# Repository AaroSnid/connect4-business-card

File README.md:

# Connect 4 Business Card

This business card doubles as a portable, handheld gaming device that allows a user to play game of Connect 4 against an onboard AI bot. Built on the STM32 platform, it features a custom 7x6 bicolor LED grid and a low-leakage power system designed for maximizing battery life.

> **Status:** Hardware V1.0 Release 
> **Hardware Version:** V1.0

---

## Features

- **Strategic Gameplay**
  - Play against a programmed AI bot on a microcontroller. You can select the difficulty and starting player through startup configurations.
  - 7x6 bicolor LED grid representing the game board. Player pieces are shown in Red / Orange

- **Dual Power Options**
  - **Battery Mode:** Optimized for a CR2032 coin cell for maximum portability.
  - **High-Performance Mode:** USB-C power input automatically boosts clock frequency for faster AI move processing. (Upcoming)

- **Power Management**
  - Physical slide switch for hard battery disconnection to prevent leakage current.
  - Integrated under-voltage and brown-out protection (BOR/POR/PDR).

- **Advanced Display Control**
  - 42 bicolor LEDs (84 total elements) routed antiparallel for layout efficiency.
  - Hardware-accelerated screen refreshing using timer triggered DMA writes to minimize CPU overhead.

- **Optimized Inputs**
  - 7 dedicated column buttons for move selection.
  - Software debouncing by limiting input registration windows.

---

## Bill of Materials (Summary)

| Item             | Part Number           | Qty | Notes                          |
|------------------|-----------------------|-----|--------------------------------|
| MCU              | STM32U073CCU6         | 1   | Ultra-low-power ARM Cortex-M0+ |
| Bicolor LEDs     | P4-1615ROTCA1-0.6T    | 42  | Red/Orange SMD LEDs            |
| Battery Holder   | Keystone 3002         | 1   | For CR2032 Coin Cell           |
| USB-C Connector  | SHOU HAN C2765186     | 1   | 16-pin Power/Data Delivery     |
| LDO Regulator    | MCP1700T-3002E/TT     | 1   | Low Quiescent Current 3.0V     |
| Input Buttons    | TSB008A2518A          | 7   | Ultra-thin NO buttons          |
| Power Switch     | MSK12C02-HB           | 1   | Battery/USB-C Selection        |

---

## Hardware Subsystems

### Power Supply

- **Primary:** CR2032 Coin Cell.
- **Secondary:** USB-C (5V) regulated through an MCP1700 LDO.
- **Switching:** A physical SPDT switch toggles between sources. The "ON" position selects the battery, while "OFF" selects USB-C, ensuring the battery is physically disconnected when using external power.
- **Monitoring:** The STM32 utilizes its internal POR/PDR/BOR peripherals to monitor voltage levels and provide under-voltage protection.

---

### Microcontroller (STM32U073CCU6)

- **Architecture:** Ultra-low-power high-performance MCU.
- **Clock Management:** (Upcoming)
  - **Battery Mode:** Lower frequency to conserve energy.
  - **USB Mode:** Increased clock frequency for "intense" AI computation.

**Key Peripherals**

| Function         | Peripheral      | Notes                                  |
|------------------|-----------------|----------------------------------------|
| LED Matrix       | GPIO Port B     | Direct register writes for speed       |
| Refresh Timing   | Hardware Timer  | Triggers DMA transfers                 |
| Data Transfer    | DMA             | Automated GPIO updates                 |
| User Inputs      | EXTI (1-7)      | Pull-down resistors on Port A          |
| Firmware Update  | USB-C (DFU)     | Native USB 2.0 bootloader support      |
| Debug            | SWD             | Standard programming interface         |

---

### Display Implementation

The display consists of 42 bicolor LEDs wired in an antiparallel configuration.
- **Efficiency:** LEDs share pins to reduce the required GPIO count.
- **Refresh Logic:** A hardware timer triggers a DMA stream that performs direct register writes to GPIO Port B. This ensures a flicker-free display without taxing the main CPU core.

---

### Inputs & UI

- **Buttons:** 7 tactile switches corresponding to the 7 columns of the Connect 4 board.
- **Debouncing:** Handled via software flags within an Interrupt Service Routine (ISR). The system clears the flag just before the player turn for software input debouncing.

---

## Firmware Architecture

### Overview

The firmware is designed for efficiency and responsiveness. 
On startup, the MCU reads the buttons to get startup config values. The rightmost button will select the AI going first, and the others select the difficulty from 1-6 (default 5)
The main game loop handles the Connect-4 logic, while the display refresh is handled entirely in the background via timer triggered DMA.

### Programming

- **Debug:** A standard SWD header is provided for real-time debugging and initial flashing.

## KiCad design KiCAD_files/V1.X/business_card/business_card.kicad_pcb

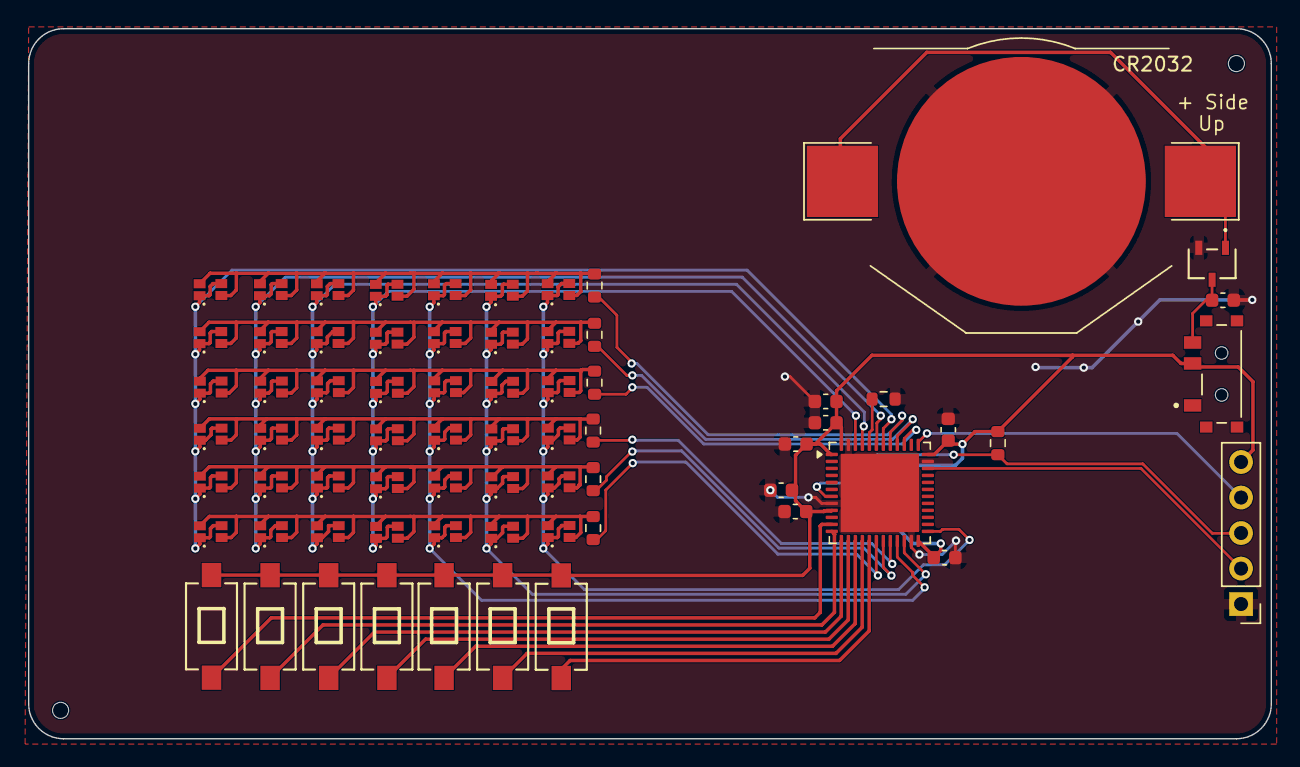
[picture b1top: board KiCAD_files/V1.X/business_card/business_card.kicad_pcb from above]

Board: 2 copper layers, 88.9 x 50.8 mm, 72 parts (0 on the bottom side), 35 nets.

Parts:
BT1: CR2032; BatteryHolder_Keystone_3002_1x2032
C1: 47uF; C_0603_1608Metric
C5, C10: 4.7uF; C_0603_1608Metric
C6, C7, C11: 100nF; C_0603_1608Metric
C8: 10nF; C_0603_1608Metric
C9: 1uF; C_0603_1608Metric
D1, D2, D3, D4, D5, D6, D7, D8, D9, D10, D11, D12, D13, D14, D15, D16, D17, D18, D19, D20, D21, D22, D23, D24, D25, D26, D27, D28, D29, D30, D31, D32, D33, D34, D35, D36, D37, D38, D39, D40, D41, D42: LED_CHIP
H1, H1#2: MountingHole; ToolingHole_1.152mm
J2: Conn_01x05_Pin; PinHeader_1x05_P2.54mm_Vertical
Q1: AO3401A; SOT-23-3L_AOS-L
R3, R4, R5, R6, R7, R8: 250; R_0603_1608Metric
R9, R10: 10K; R_0603_1608Metric
S1: MSK12C02; SW_MSK12C02
SW1, SW2, SW3, SW4, SW5, SW6, SW7: SW_Push; TSB008A2526A
U1: STM32U073CCUx; QFN-48-1EP_7x7mm_P0.5mm_EP5.6x5.6mm

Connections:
/COL1: D1.1, D1.3, D8.1, D8.3, D15.1, D15.3, D22.1, D22.3, D29.1, D29.3, D36.1, D36.3, U1.42 (PB6)
/COL2: D2.1, D2.3, D9.1, D9.3, D16.1, D16.3, D23.1, D23.3, D30.1, D30.3, D37.1, D37.3, U1.43 (PB7)
/COL3: D3.1, D3.3, D10.1, D10.3, D17.1, D17.3, D24.1, D24.3, D31.1, D31.3, D38.1, D38.3, U1.45 (PB8)
/COL4: D4.1, D4.3, D11.1, D11.3, D18.1, D18.3, D25.1, D25.3, D32.1, D32.3, D39.1, D39.3, U1.46 (PB9)
/COL5: D5.1, D5.3, D12.1, D12.3, D19.1, D19.3, D26.1, D26.3, D33.1, D33.3, D40.1, D40.3, U1.21 (PB10)
/COL6: D6.1, D6.3, D13.1, D13.3, D20.1, D20.3, D27.1, D27.3, D34.1, D34.3, D41.1, D41.3, U1.22 (PB11)
/COL7: D7.1, D7.3, D14.1, D14.3, D21.1, D21.3, D28.1, D28.3, D35.1, D35.3, D42.1, D42.3, U1.25 (PB12)
/INPUT_1: SW1.1, U1.11 (PA1)
/INPUT_2: SW2.1, U1.12 (PA2)
/INPUT_3: SW3.1, U1.13 (PA3)
/INPUT_4: SW4.1, U1.14 (PA4)
/INPUT_5: SW5.1, U1.15 (PA5)
/INPUT_6: SW6.1, U1.16 (PA6)
/INPUT_7: SW7.1, U1.17 (PA7)
/NRST: J2.3, R10.2, U1.7 (PF2)
/ROW1: R3.2, U1.41 (PB5)
/ROW2: R4.2, U1.40 (PB4)
/ROW3: R5.2, U1.39 (PB3)
/ROW4: R6.2, U1.20 (PB2)
/ROW5: R7.2, U1.19 (PB1)
/ROW6: R8.2, U1.18 (PB0)
/SWCLK: J2.4, U1.37 (PA14)
/SWDIO: J2.2, U1.34 (PA13)
GND: BT1.2 (-), C1.2, C5.2, C6.2, C7.2, C8.2, C9.2, C10.2, C11.2, J2.1, Q1.2 (G), R9.2, U1.8 (VSSA), U1.23 (VSS), U1.35 (VSS), U1.47 (VSS), U1.49 (VSS)
unnamed: BT1.1 (+), Q1.1 (D)
unnamed: D1.2, D1.4, D2.2, D2.4, D3.2, D3.4, D4.2, D4.4, D5.2, D5.4, D6.2, D6.4, D7.2, D7.4, R3.1
unnamed: D8.2, D8.4, D9.2, D9.4, D10.2, D10.4, D11.2, D11.4, D12.2, D12.4, D13.2, D13.4, D14.2, D14.4, R4.1
unnamed: D15.2, D15.4, D16.2, D16.4, D17.2, D17.4, D18.2, D18.4, D19.2, D19.4, D20.2, D20.4, D21.2, D21.4, R5.1
unnamed: D22.2, D22.4, D23.2, D23.4, D24.2, D24.4, D25.2, D25.4, D26.2, D26.4, D27.2, D27.4, D28.2, D28.4, R6.1
unnamed: D29.2, D29.4, D30.2, D30.4, D31.2, D31.4, D32.2, D32.4, D33.2, D33.4, D34.2, D34.4, D35.2, D35.4, R7.1
unnamed: D36.2, D36.4, D37.2, D37.4, D38.2, D38.4, D39.2, D39.4, D40.2, D40.4, D41.2, D41.4, D42.2, D42.4, R8.1
unnamed: C1.1, Q1.3 (S), S1.3
unnamed: S1.4_1 (GND), S1.4_2 (GND), S1.4_3 (GND), S1.4_4 (GND)
unnamed: R9.1, U1.44 (PF3)
VDD: C5.1, C6.1, C7.1, C8.1, C9.1, C10.1, C11.1, J2.5, R10.1, S1.2, SW1.2, SW2.2, SW3.2, SW4.2, SW5.2, SW6.2, SW7.2, U1.1 (VBAT), U1.9 (VDDA), U1.24 (VDD), U1.36 (VDDUSB), U1.48 (VDD)

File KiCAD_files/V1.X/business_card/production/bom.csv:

Designator,Footprint,Quantity,Value,LCSC Part #
BT1,BatteryHolder_Keystone_3002_1x2032,1,CR2032,
"C1, C10, C5",0603,3,4.7uF,
"C11, C6, C7",0603,3,100nF,
"C2, C3, C4, C9",0603,4,1uF,
C8,0603,1,10nF,
"D1, D10, D11, D12, D13, D14, D15, D16, D17, D18, D19, D2, D20, D21, D22, D23, D24, D25, D26, D27, D28, D29, D3, D30, D31, D32, D33, D34, D35, D36, D37, D38, D39, D4, D40, D41, D42, D5, D6, D7, D8, D9",LED_CHIP,42,~,
J1,USB-C-SMD_TYPE-C-6PIN-2MD-073,1,USB_C_Receptacle_USB2.0_14P,
J2,PinHeader_1x05_P1.00mm_Vertical,1,Conn_01x05_Pin,
"R1, R2",0603,2,5.1K,
"R10, R9",0603,2,10K,
"R3, R4, R5, R6, R7, R8",0603,6,250,
S1,SW_MSK12C02,1,MSK12C02,
"SW1, SW2, SW3, SW4, SW5, SW6, SW7",TSB008A2526A,7,SW_Push,
SW8,SW-SMD_4P-L2.6-W1.6-P0.75-LS3.0,1,SW_MEC_5E,
TP1,TestPoint_THTPad_D1.0mm_Drill0.5mm,1,VDDUSB,
TP2,TestPoint_THTPad_D1.0mm_Drill0.5mm,1,GND,
TP3,TestPoint_THTPad_D1.0mm_Drill0.5mm,1,VDD,
U1,QFN-48-1EP_7x7mm_P0.5mm_EP5.6x5.6mm,1,STM32U073CCUx,
U2,SOT-23,1,MCP1700x-300xxTT,

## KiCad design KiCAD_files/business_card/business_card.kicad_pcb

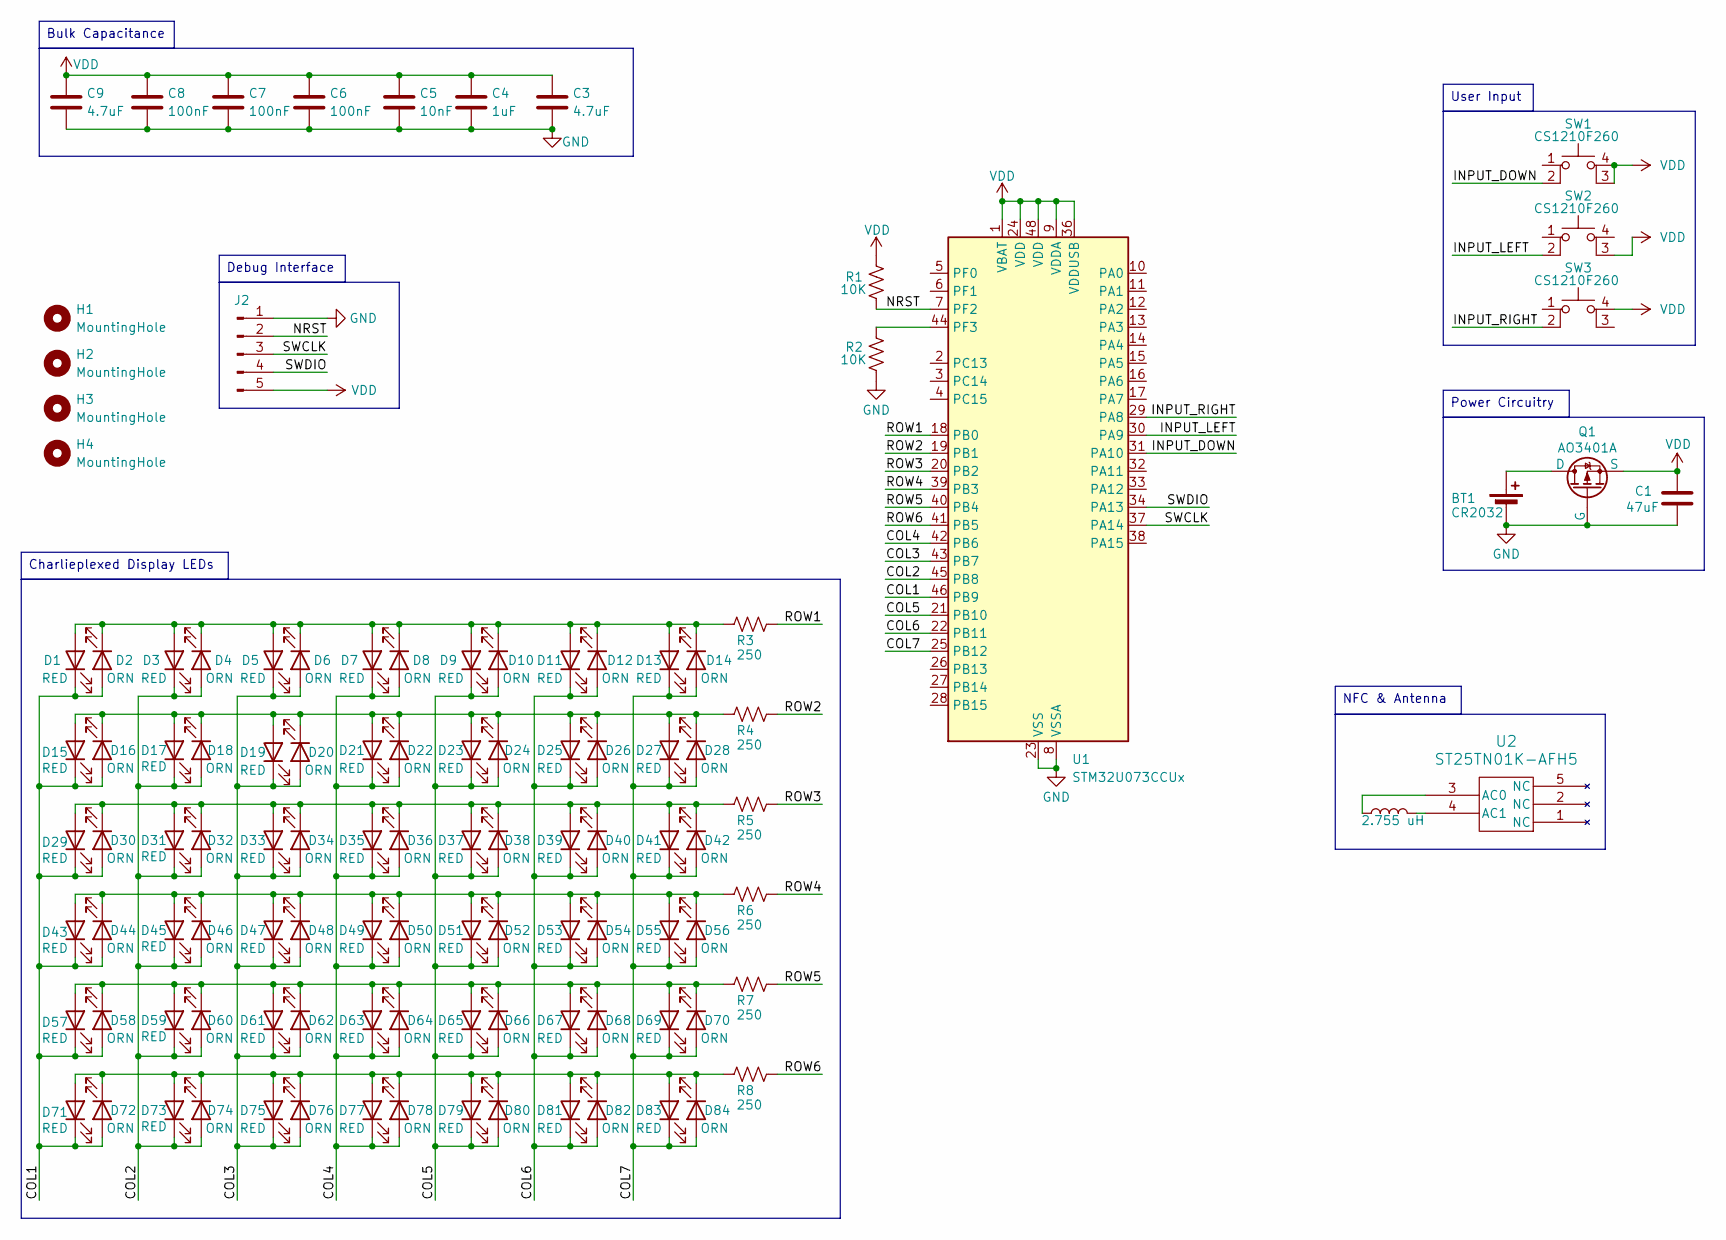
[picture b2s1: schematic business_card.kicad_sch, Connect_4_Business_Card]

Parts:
BT1: CR2032; BAT_BAT-HLD-005-THM
C1: 47uF; C_0603_1608Metric
C3, C9: 4.7uF; C_0603_1608Metric
C4: 1uF; C_0603_1608Metric
C5: 10nF; C_0603_1608Metric
C6, C7, C8: 100nF; C_0603_1608Metric
D1, D3, D5, D7, D9, D11, D13, D15, D17, D19, D21, D23, D25, D27, D29, D31, D33, D35, D37, D39, D41, D43, D45, D47, D49, D51, D53, D55, D57, D59, D61, D63, D65, D67, D69, D71, D73, D75, D77, D79, D81, D83: RED; LED_0603_1608Metric
D2, D4, D6, D8, D10, D12, D14, D16, D18, D20, D22, D24, D26, D28, D30, D32, D34, D36, D38, D40, D42, D44, D46, D48, D50, D52, D54, D56, D58, D60, D62, D64, D66, D68, D70, D72, D74, D76, D78, D80, D82, D84: ORN; LED_0603_1608Metric
H1, H2, H3, H4: MountingHole; ToolingHole_1.152mm
J2: Conn_01x05_Pin; PinHeader_1x05_P2.54mm_Vertical
L1: 2.755 uH; 25X48MM_NFC
Q1: AO3401A; SOT-23-3L_AOS-L
R1, R2: 10K; R_0603_1608Metric
R3, R4, R5, R6, R7, R8: 250; R_0603_1608Metric
SW1, SW2, SW3: CS1210F260; SW4_CS1210F260_CRS
U1: STM32U073CCUx; QFN-48-1EP_7x7mm_P0.5mm_EP5.6x5.6mm
U2: ST25TN01K-AFH5; UFDFPN-5_1P8X1P5_STM

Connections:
/COL1: D1.1 (K), D2.2 (A), D15.1 (K), D16.2 (A), D29.1 (K), D30.2 (A), D43.1 (K), D44.2 (A), D57.1 (K), D58.2 (A), D71.1 (K), D72.2 (A), U1.46 (PB9)
/COL2: D3.1 (K), D4.2 (A), D17.1 (K), D18.2 (A), D31.1 (K), D32.2 (A), D45.1 (K), D46.2 (A), D59.1 (K), D60.2 (A), D73.1 (K), D74.2 (A), U1.45 (PB8)
/COL3: D5.1 (K), D6.2 (A), D19.1 (K), D20.2 (A), D33.1 (K), D34.2 (A), D47.1 (K), D48.2 (A), D61.1 (K), D62.2 (A), D75.1 (K), D76.2 (A), U1.43 (PB7)
/COL4: D7.1 (K), D8.2 (A), D21.1 (K), D22.2 (A), D35.1 (K), D36.2 (A), D49.1 (K), D50.2 (A), D63.1 (K), D64.2 (A), D77.1 (K), D78.2 (A), U1.42 (PB6)
/COL5: D9.1 (K), D10.2 (A), D23.1 (K), D24.2 (A), D37.1 (K), D38.2 (A), D51.1 (K), D52.2 (A), D65.1 (K), D66.2 (A), D79.1 (K), D80.2 (A), U1.21 (PB10)
/COL6: D11.1 (K), D12.2 (A), D25.1 (K), D26.2 (A), D39.1 (K), D40.2 (A), D53.1 (K), D54.2 (A), D67.1 (K), D68.2 (A), D81.1 (K), D82.2 (A), U1.22 (PB11)
/COL7: D13.1 (K), D14.2 (A), D27.1 (K), D28.2 (A), D41.1 (K), D42.2 (A), D55.1 (K), D56.2 (A), D69.1 (K), D70.2 (A), D83.1 (K), D84.2 (A), U1.25 (PB12)
/INPUT_DOWN: SW1.2, U1.31 (PA10)
/INPUT_LEFT: SW2.2, U1.30 (PA9)
/INPUT_RIGHT: SW3.2, U1.29 (PA8)
/NRST: J2.2, R1.2, U1.7 (PF2)
/ROW1: R3.2, U1.18 (PB0)
/ROW2: R4.2, U1.19 (PB1)
/ROW3: R5.2, U1.20 (PB2)
/ROW4: R6.2, U1.39 (PB3)
/ROW5: R7.2, U1.40 (PB4)
/ROW6: R8.2, U1.41 (PB5)
/SWCLK: J2.3, U1.37 (PA14)
/SWDIO: J2.4, U1.34 (PA13)
GND: BT1.2 (-), C1.2, C3.2, C4.2, C5.2, C6.2, C7.2, C8.2, C9.2, J2.1, Q1.2 (G), R2.2, U1.8 (VSSA), U1.23 (VSS), U1.35 (VSS), U1.47 (VSS), U1.49 (VSS)
unnamed: BT1.1 (+), Q1.1 (D)
unnamed: D1.2 (A), D2.1 (K), D3.2 (A), D4.1 (K), D5.2 (A), D6.1 (K), D7.2 (A), D8.1 (K), D9.2 (A), D10.1 (K), D11.2 (A), D12.1 (K), D13.2 (A), D14.1 (K), R3.1
unnamed: D15.2 (A), D16.1 (K), D17.2 (A), D18.1 (K), D19.2 (A), D20.1 (K), D21.2 (A), D22.1 (K), D23.2 (A), D24.1 (K), D25.2 (A), D26.1 (K), D27.2 (A), D28.1 (K), R4.1
unnamed: D29.2 (A), D30.1 (K), D31.2 (A), D32.1 (K), D33.2 (A), D34.1 (K), D35.2 (A), D36.1 (K), D37.2 (A), D38.1 (K), D39.2 (A), D40.1 (K), D41.2 (A), D42.1 (K), R5.1
unnamed: D43.2 (A), D44.1 (K), D45.2 (A), D46.1 (K), D47.2 (A), D48.1 (K), D49.2 (A), D50.1 (K), D51.2 (A), D52.1 (K), D53.2 (A), D54.1 (K), D55.2 (A), D56.1 (K), R6.1
unnamed: D57.2 (A), D58.1 (K), D59.2 (A), D60.1 (K), D61.2 (A), D62.1 (K), D63.2 (A), D64.1 (K), D65.2 (A), D66.1 (K), D67.2 (A), D68.1 (K), D69.2 (A), D70.1 (K), R7.1
unnamed: D71.2 (A), D72.1 (K), D73.2 (A), D74.1 (K), D75.2 (A), D76.1 (K), D77.2 (A), D78.1 (K), D79.2 (A), D80.1 (K), D81.2 (A), D82.1 (K), D83.2 (A), D84.1 (K), R8.1
unnamed: R2.1, U1.44 (PF3)
unnamed: L1.1, U2.3 (AC0)
unnamed: L1.2, U2.4 (AC1)
VDD: C1.1, C3.1, C4.1, C5.1, C6.1, C7.1, C8.1, C9.1, J2.5, Q1.3 (S), R1.1, SW1.3 (K), SW1.4 (A), SW2.3 (K), SW3.4 (A), U1.1 (VBAT), U1.9 (VDDA), U1.24 (VDD), U1.36 (VDDUSB), U1.48 (VDD)

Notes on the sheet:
Bulk Capacitance
Charlieplexed Display LEDs
Power Circuitry
User Input
NFC & Antenna
Debug Interface

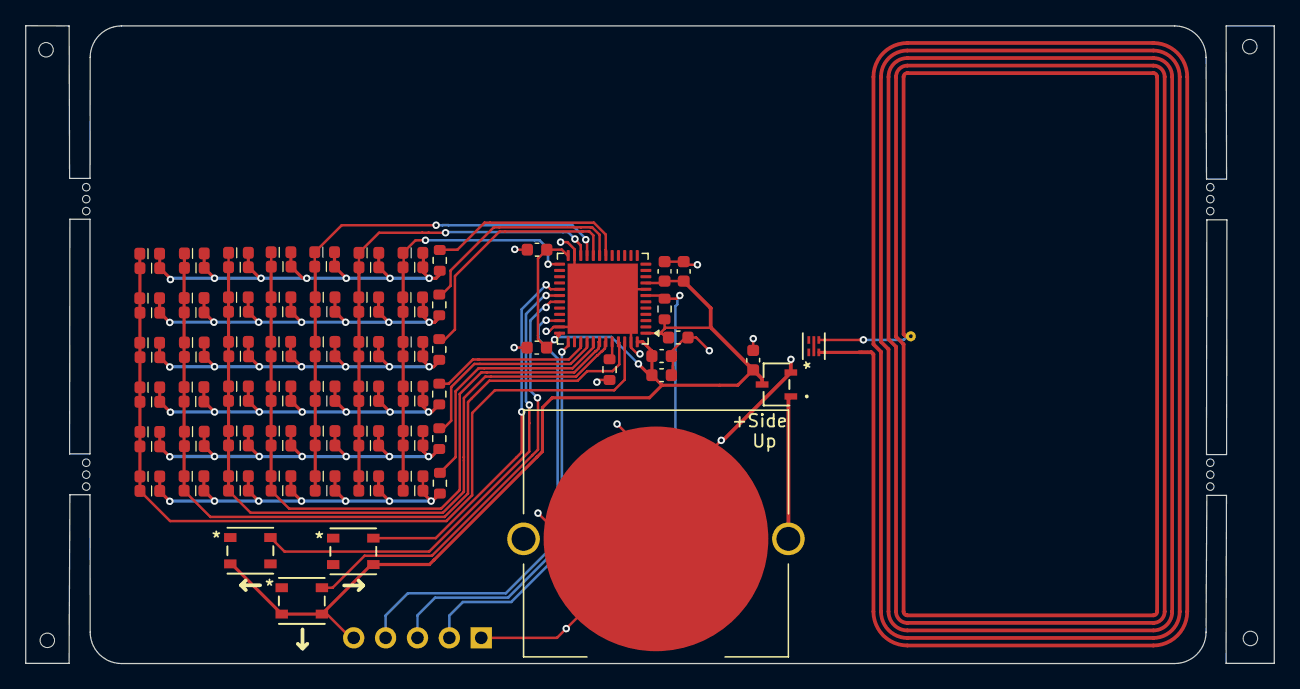
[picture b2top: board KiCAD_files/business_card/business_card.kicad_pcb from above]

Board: 2 copper layers, 99.5 x 50.8 mm, 113 parts (0 on the bottom side), 31 nets.

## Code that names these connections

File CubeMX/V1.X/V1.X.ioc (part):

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Mcu.Name=STM32U073CCUx
Mcu.Package=UFQFPN48
Mcu.UserName=STM32U073CCUx
PA1.GPIOParameters=GPIO_PuPd,GPIO_Label
PA1.GPIO_Label=INPUT_1
PA1.GPIO_PuPd=GPIO_PULLDOWN
PA1.Signal=GPXTI1
PA2.GPIOParameters=GPIO_PuPd,GPIO_Label
PA2.GPIO_Label=INPUT_2
PA2.GPIO_PuPd=GPIO_PULLDOWN
PA2.Signal=GPXTI2
PA3.GPIOParameters=GPIO_PuPd,GPIO_Label
PA3.GPIO_Label=INPUT_3
PA3.GPIO_PuPd=GPIO_PULLDOWN
PA3.Signal=GPXTI3
PA4.GPIOParameters=GPIO_PuPd,GPIO_Label
PA4.GPIO_Label=INPUT_4
PA4.GPIO_PuPd=GPIO_PULLDOWN
PA4.Signal=GPXTI4
PA5.GPIOParameters=GPIO_PuPd,GPIO_Label
PA5.GPIO_Label=INPUT_5
PA5.GPIO_PuPd=GPIO_PULLDOWN
PA5.Signal=GPXTI5
PA6.GPIOParameters=GPIO_PuPd,GPIO_Label
PA6.GPIO_Label=INPUT_6
PA6.GPIO_PuPd=GPIO_PULLDOWN
PA6.Signal=GPXTI6
PA7.GPIOParameters=GPIO_PuPd,GPIO_Label
PA7.GPIO_Label=INPUT_7
PA7.GPIO_PuPd=GPIO_PULLDOWN
PA7.Signal=GPXTI7
PA8.GPIOParameters=GPIO_PuPd,GPIO_Label
PA8.GPIO_Label=USB_INPUT
PA8.GPIO_PuPd=GPIO_PULLDOWN
PA8.Signal=GPIO_Input
RCC.HSE_VALUE=4000000
RCC.SYSCLKFreq_VALUE=16000000
board=custom

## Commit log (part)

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2026-03-17 Initial Circuit Diagram For PCB
2026-03-17 Clean Up Files and Add Footprints
2026-03-17 Add Debug Interface and Test Points
2026-03-18 Update Footprints of Components and Start Layout Design
2026-03-19 Change Connections to Match STM32C0 Spec
2026-03-19 Move Battery Voltage Monitoring to Software
2026-03-20 Switch Button types, Add 3D Models to Components
2026-03-25 PCB Layout
2026-03-25 Fix Edge Cuts
2026-03-25 Fix Ground Fill
2026-03-28 Finish Initial PCB Layout
2026-03-28 Fix Small Connection Issues
2026-04-01 Add Contact Info
2026-04-25 Add Project Description
2026-04-25 Add Image to READme
2026-04-29 V1.0 Hardware Production Version Out For Assembly
2026-05-03 Initial Schematic for V2.0
2026-05-03 Initial V2.0 Layout
2026-05-03 Change Button in Schematic and Footprint
2026-05-05 Initial Layout for V2.0
2026-05-06 Add NFC Antenna
2026-05-07 Adjust LED Matrix Size
2026-05-07 Add Mouse Bites to Isolate Tooling Holes
2026-05-07 Move Components and Remove Unnecessary Silkscreen
2026-05-13 Restructure Media Files
2026-05-15 Initial STM32 IOC File Setup
2026-05-16 Set Up DMA at 400Hz refresh rate
2026-05-24 Generate Code from Initial .ioc File
2026-05-25 Change Debug Interface Connector Size
2026-05-26 Set Up CMake Project
2026-05-26 Set Up Power Supply Voltage Monitoring
2026-05-27 Add PushButton Inputs Using Interrupt Lines
2026-05-28 Add V1.0 Board Photos
2026-05-29 Add Card Picture to Readme
2026-06-23 Add Screen Buffer Defines and Variables
2026-06-24 Set Up LED Screen DMA Transaction
2026-06-26 Change Order of Charlieplexing Scan to Match Connect-4 Algorithm Bitboard
